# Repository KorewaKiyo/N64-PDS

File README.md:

# N64-PDS
## A USB-PD PSU for the Nintendo 64
This project aims to replace the bulky AC power supply of the n64 with a small, flush USB-PD supply.

The board is currently in V1 prototyping stage,
It will currently only support 15v supplies, though 5,9,15 are intended to be supported.
### Board view

rendered with [kicad-render](https://github.com/linalinn/kicad-render)

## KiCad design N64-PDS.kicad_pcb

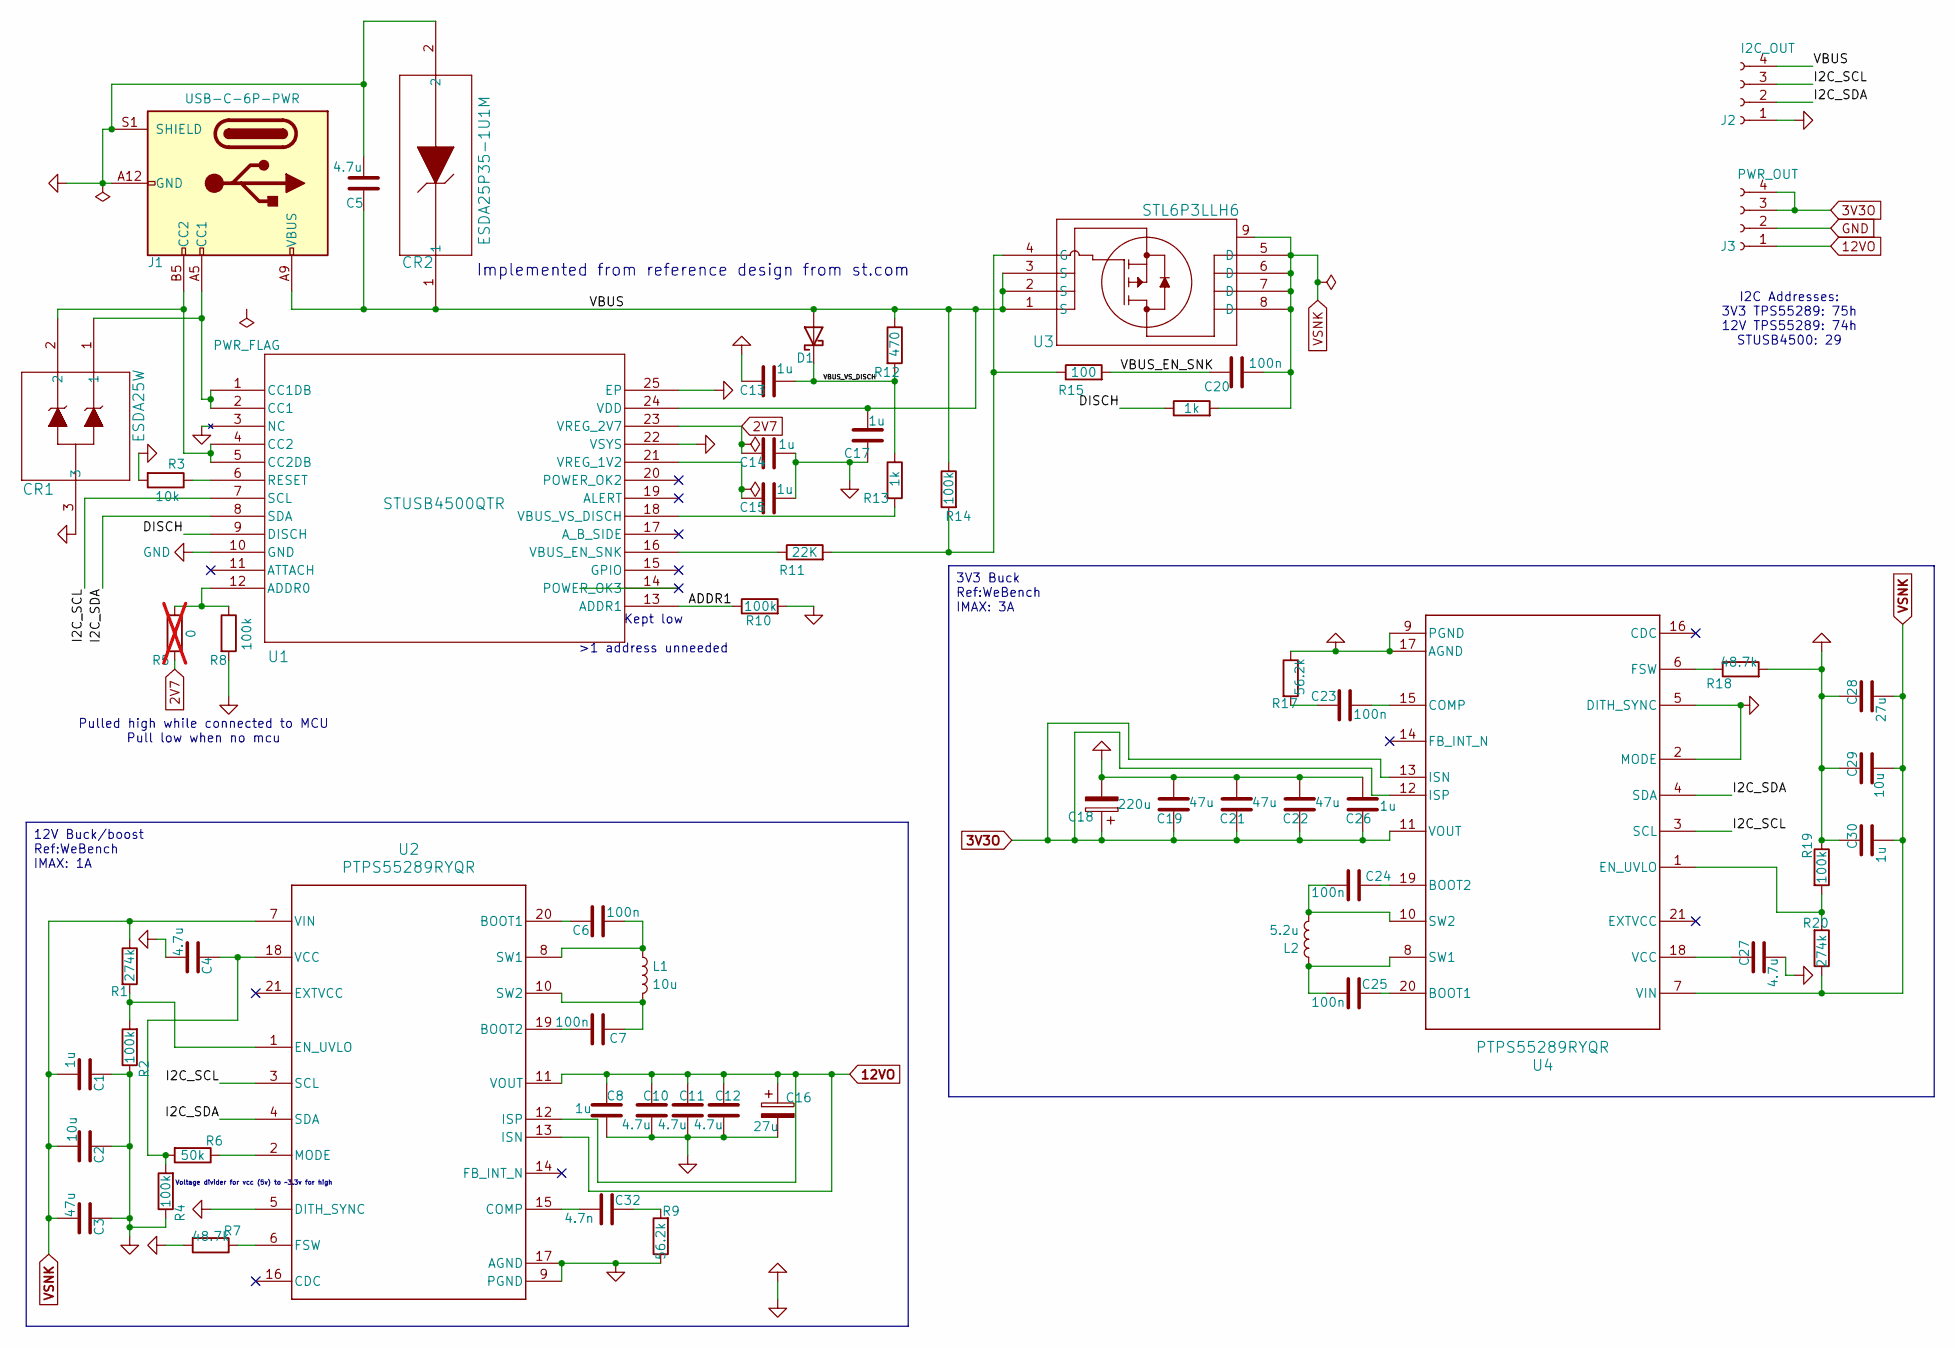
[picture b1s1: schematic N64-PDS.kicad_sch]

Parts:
C1, C13, C14, C15, C17, C30: 1u; C_0402_1005Metric_Pad0.74x0.62mm_HandSolder
C2, C29: 10u; C_1210_3225Metric_Pad1.33x2.70mm_HandSolder
C3: 47u; C_Elec_6.3x5.8
C4, C27: 4.7u; C_0603_1608Metric_Pad1.08x0.95mm_HandSolder
C5, C10, C11, C12: 4.7u; C_0805_2012Metric_Pad1.18x1.45mm_HandSolder
C6, C7, C24, C25: 100n; C_0603_1608Metric_Pad1.08x0.95mm_HandSolder
C8, C26: 1u; C_0603_1608Metric_Pad1.08x0.95mm_HandSolder
C16: 27u; CP_Elec_5x5.9
C18: 220u; CP_Elec_6.3x5.9
C19, C21, C22: 47u; C_0805_2012Metric_Pad1.18x1.45mm_HandSolder
C20: 100n; C_0504_1310Metric_Pad0.83x1.28mm_HandSolder
C23: 100n; C_0402_1005Metric_Pad0.74x0.62mm_HandSolder
C28: 27u; C_Elec_5x5.8
C32: 4.7n; C_0402_1005Metric_Pad0.74x0.62mm_HandSolder
CR1: ESDA25W; SOT323-3L_STM-M
CR2: ESDA25P35-1U1M; QFN1610_STM-M
D1: D_0402_1005Metric_Pad0.77x0.64mm_HandSolder
J1: USB-C-6P-PWR; USB_C_Receptacle_GCT_USB4125-xx-x-0190_6P_TopMnt_Horizontal
J2: I2C_OUT; Molex_PicoBlade_53047-0410_1x04_P1.25mm_Vertical
J3: PWR_OUT; JST_NV_B04P-NV_1x04_P5.00mm_Vertical
L1: 10u; DR1040-5R2-R
L2: 5.2u; L_Coilcraft_XAL6060-XXX
R1, R20: 274k; R_0402_1005Metric_Pad0.72x0.64mm_HandSolder
R2, R4, R8, R10, R14, R19: 100k; R_0402_1005Metric_Pad0.72x0.64mm_HandSolder
R3: 10k; R_0402_1005Metric_Pad0.72x0.64mm_HandSolder
R5: 0; R_0402_1005Metric_Pad0.72x0.64mm_HandSolder; not fitted
R6: 50k; R_0402_1005Metric_Pad0.72x0.64mm_HandSolder
R7, R18: 48.7k; R_0402_1005Metric_Pad0.72x0.64mm_HandSolder
R9, R17: 56.2k; R_0402_1005Metric_Pad0.72x0.64mm_HandSolder
R11: 22K; R_0402_1005Metric_Pad0.72x0.64mm_HandSolder
R12: 470; R_0402_1005Metric_Pad0.72x0.64mm_HandSolder
R13, R16: 1k; R_0402_1005Metric_Pad0.72x0.64mm_HandSolder
R15: 100; R_0402_1005Metric_Pad0.72x0.64mm_HandSolder
U1: STUSB4500QTR; QFN24EP_4X4_STM-M
U2, U4: PTPS55289RYQR; RYQ0021A-MFG
U3: STL6P3LLH6; POWERFLAT_3P3X3P3_STM

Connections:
2V7: C14.1, R5.2, U1.23 (VREG_2V7)
3V3O: C18.1, C19.2, C21.2, C22.2, C26.2, J3.3, J3.4, U4.11 (VOUT), U4.12 (ISP), U4.13 (ISN)
12VO: C8.2, C10.2, C11.2, C12.2, C16.1, J3.1, U2.11 (VOUT), U2.12 (ISP), U2.13 (ISN)
/ADDR1: R10.1, U1.13 (ADDR1)
/DISCH: R16.1, U1.9 (DISCH)
/I2C_SCL: J2.3, U1.7 (SCL), U2.3 (SCL), U4.3 (SCL)
/I2C_SDA: J2.2, U1.8 (SDA), U2.4 (SDA), U4.4 (SDA)
/VBUS: C5.1, C17.1, CR2.1, D1.2 (A), J1.A9 (VBUS), J1.B9 (VBUS), J2.4, R12.1, R14.1, U1.24 (VDD), U3.1 (S), U3.2 (S), U3.3 (S)
/VBUS_EN_SNK: C20.1, R15.2
/VBUS_VS_DISCH: C13.2, D1.1 (K), R12.2, R13.1
GND: C1.2, C2.2, C3.2, C4.1, C5.2, C8.1, C10.1, C11.1, C12.1, C13.1, C14.2, C15.2, C16.2, C17.2, C18.2, C19.1, C21.1, C22.1, C26.1, C27.1, C28.2, C29.2, C30.2, CR1.3, CR2.2, J1.A12 (GND), J1.B12 (GND), J1.S1 (SHIELD), J2.1, J3.2, R2.1, R3.2, R4.1, R7.2, R8.2, R9.1, R10.2, R17.1, R18.2, R19.1, U1.3 (NC), U1.10 (GND), U1.22 (VSYS), U1.25 (EP), U2.5 (DITH_SYNC), U2.9 (PGND), U2.17 (AGND), U4.2 (MODE), U4.5 (DITH_SYNC), U4.9 (PGND), U4.17 (AGND)
unnamed: C23.1, R17.2
unnamed: C32.1, R9.2
unnamed: CR1.1, J1.A5 (CC1), U1.1 (CC1DB), U1.2 (CC1)
unnamed: CR1.2, J1.B5 (CC2), U1.4 (CC2), U1.5 (CC2DB)
unnamed: R5.1, R8.1, U1.12 (ADDR0)
unnamed: R3.1, U1.6 (RESET)
unnamed: R11.1, U1.16 (VBUS_EN_SNK)
unnamed: R13.2, U1.18 (VBUS_VS_DISCH)
unnamed: C15.1, U1.21 (VREG_1V2)
unnamed: C6.1, U2.20 (BOOT1)
unnamed: C7.2, U2.19 (BOOT2)
unnamed: C32.2, U2.15 (COMP)
unnamed: R1.2, R2.2, U2.1 (EN_UVLO)
unnamed: R7.1, U2.6 (FSW)
unnamed: R6.1, U2.2 (MODE)
unnamed: C6.2, L1.1, U2.8 (SW1)
unnamed: C7.1, L1.2, U2.10 (SW2)
unnamed: C4.2, R4.2, R6.2, U2.18 (VCC)
unnamed: R11.2, R14.2, R15.1, U3.4 (G)
unnamed: C25.1, U4.20 (BOOT1)
unnamed: C24.1, U4.19 (BOOT2)
unnamed: C23.2, U4.15 (COMP)
unnamed: R19.2, R20.2, U4.1 (EN_UVLO)
unnamed: R18.1, U4.6 (FSW)
unnamed: C25.2, L2.1, U4.8 (SW1)
unnamed: C24.2, L2.2, U4.10 (SW2)
unnamed: C27.2, U4.18 (VCC)
VSNK: C1.1, C2.1, C3.1, C20.2, C28.1, C29.1, C30.1, R1.1, R16.2, R20.1, U2.7 (VIN), U3.5 (D), U3.6 (D), U3.7 (D), U3.8 (D), U3.9, U4.7 (VIN)

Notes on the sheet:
Kept low >1 address unneeded
Voltage divider for vcc (5v) to ~3.3v for high
Implemented from reference design from st.com
I2C Addresses: 3V3 TPS55289: 75h 12V TPS55289: 74h STUSB4500: 29
Pulled high while connected to MCU Pull low when no mcu
3V3 Buck Ref:WeBench IMAX: 3A
12V Buck/boost Ref:WeBench IMAX: 1A

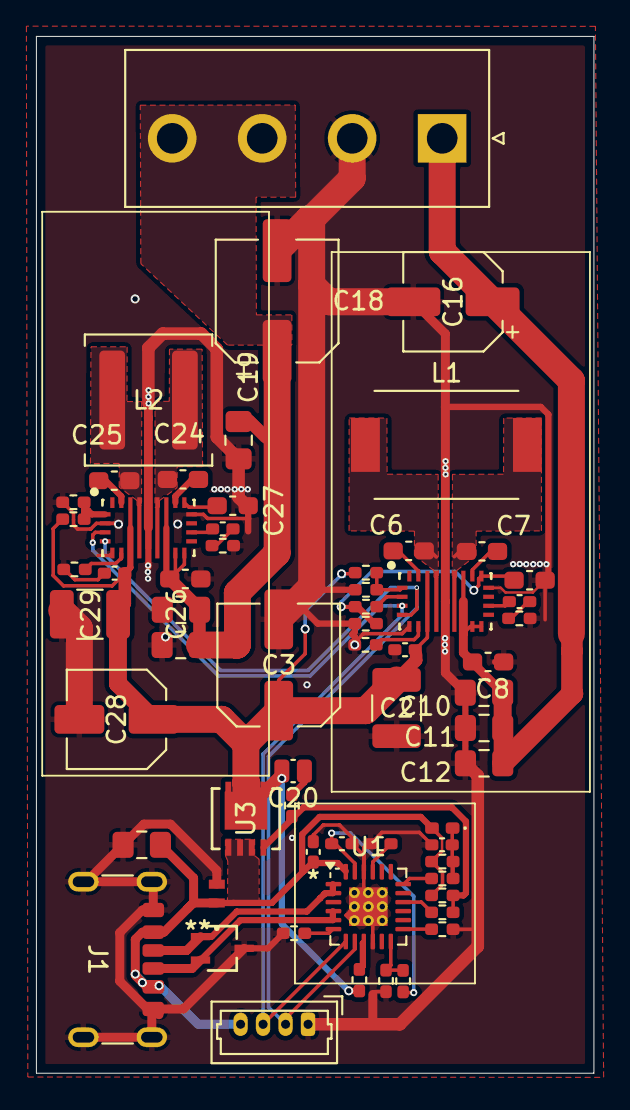
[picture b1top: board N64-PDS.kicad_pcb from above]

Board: 2 copper layers, 31.0 x 57.6 mm, 69 parts (0 on the bottom side), 39 nets.

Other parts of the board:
kibuzzard-682FAEAC: G***; kibuzzard-682FAEAC
kibuzzard-682FAEBC: G***; kibuzzard-682FAEBC
kibuzzard-682FAEC4: G***; kibuzzard-682FAEC4
kibuzzard-682FAECA: G***; kibuzzard-682FAECA
kibuzzard-682FAF0F: G***; kibuzzard-682FAF0F
kibuzzard-682FAF07: G***; kibuzzard-682FAF07
kibuzzard-682FAF25: G***; kibuzzard-682FAF25

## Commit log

2024-10-04 V1.0
    The initial finished V1 board,
    15V PD in, 3.3v and 12v out
2024-10-04 Update annotations
    Whoopsy!!
    I updated all the annotations geographically on the pcb and didnt update the schematic from the pcb, all fixed :)
2024-10-10 Update PCB
    slight reshuffle of the PCB in the aim of reducing noise from smps
2024-10-10 Re-route
    Re-route to improve design, further updates to come
2024-10-11 4Layer
    4 layer board, destroy 12v rail to make space for new 12v rail.
2024-10-11 Component switch
    Switch buck/boost converter components, Complete schematic
2024-10-17 Add footprint, assign all component footprints.
2024-10-25 Update footprints
2024-10-25 Update mosfet footprint & symbol
2024-10-25 Update board
2024-11-06 Finish board layout and routing
    Finished board layout and routing, added a hatched ground plane for looks (and some emi)
2024-11-11 Finalise PCB
    Finalise PCB, sent off to JLC for PCB fabrication.
2025-05-20 Kicad 9
2025-05-22 Oops all redesigns
    I did it again, this time smaller, better laid out, and all around maybe gooderer
2025-05-28 Groundplane tidy up
    Tidy up the backside a little to make the ground plane less segmented.
